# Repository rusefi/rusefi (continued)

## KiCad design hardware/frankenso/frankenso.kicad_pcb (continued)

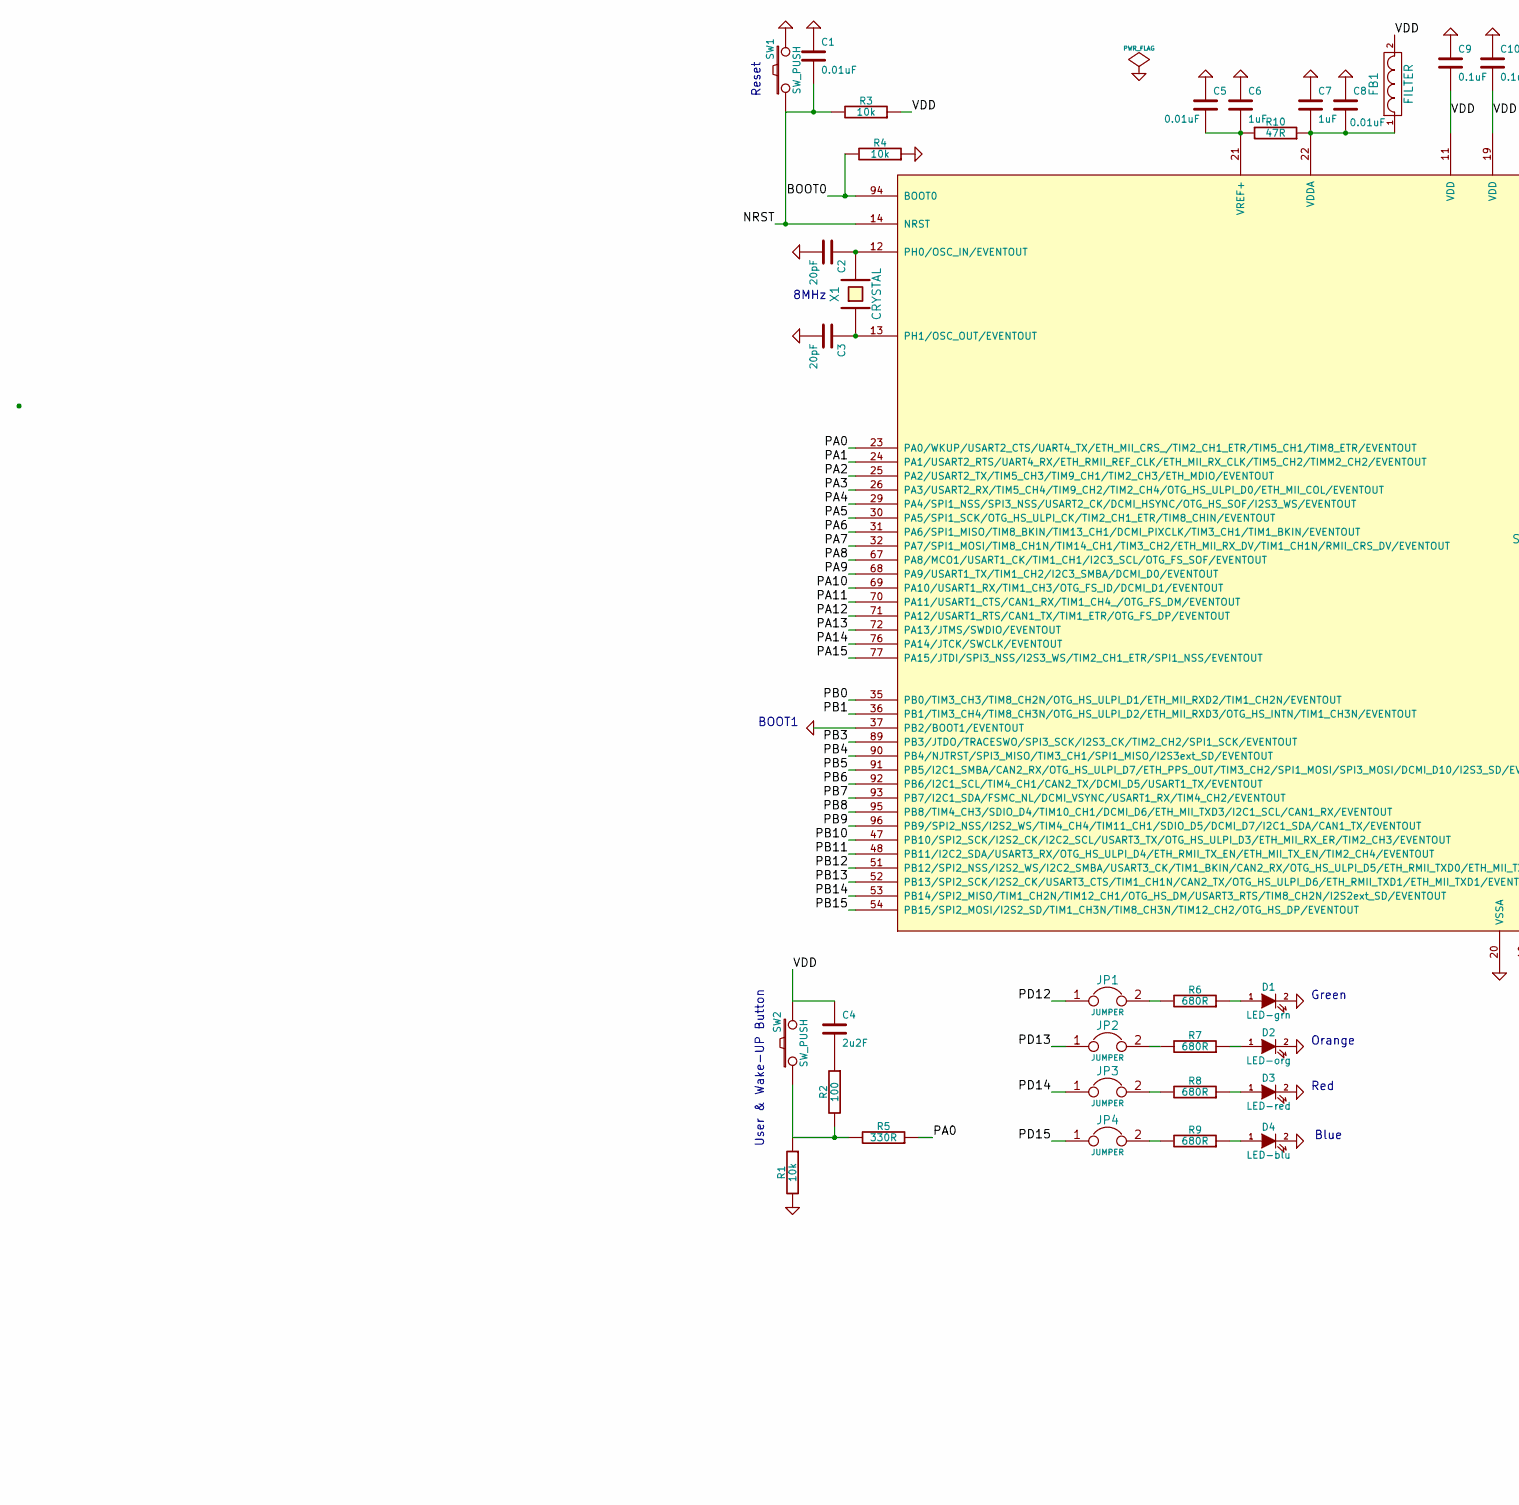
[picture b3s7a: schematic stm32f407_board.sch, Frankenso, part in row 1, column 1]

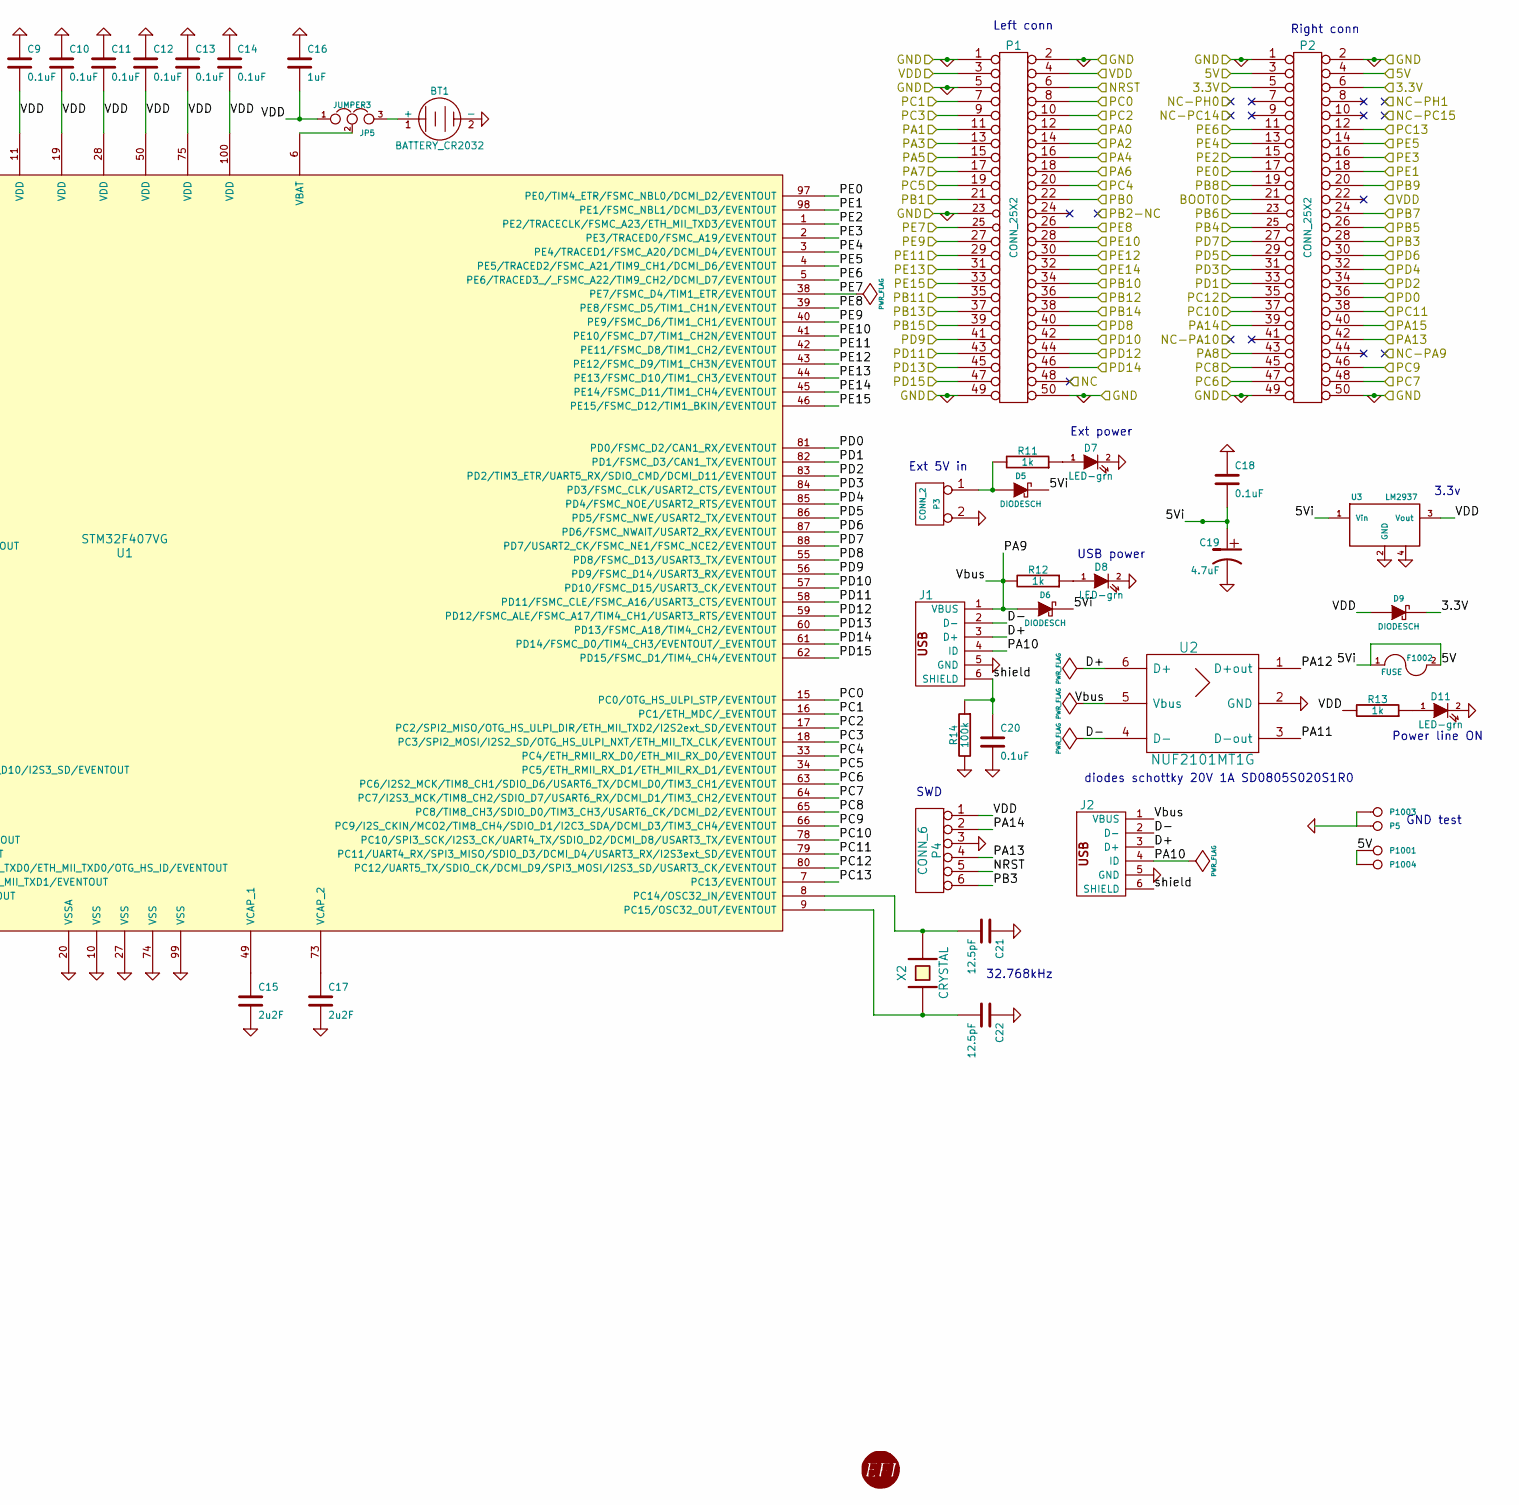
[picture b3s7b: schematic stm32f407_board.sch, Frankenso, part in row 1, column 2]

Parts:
BT1: BATTERY_CR2032; BATT_CR2032_MPD
C1, C5, C8: 0.01uF; SM0805
C2, C3: 20pF; SM0805
C4, C15, C17: 2u2F; SM0805
C6, C7, C16: 1uF; SM0805
C9, C10, C11, C12, C13, C14, C18, C20: 0.1uF; SM0805
C19: 4.7uF; SM0805
C21, C22: 12.5pF; SM0805
D1, D7, D8, D11: LED-grn; LED-0805_A
D2: LED-org; LED-0805_A
D3: LED-red; LED-0805_A
D4: LED-blu; LED-0805_A
D5, D6, D9: DIODESCH; SM0805-diode
F1002: FUSE; SM0805-diode
FB1: FILTER; SM0805
G1: LOGO; LOGO_F
J1: MINI-USB-5P-3400020P1
J2: MINI-USB-5P-3400020P1V; MINI-USB_RCTP_V-T_B
JP1, JP2, JP3, JP4: JUMPER; JUMPER-2
JP5: JUMPER3; SIL-3
P1, P2: CONN_25X2; PIN_ARRAY_25x2_A
P3: CONN_2; PIN_ARRAY_2_A
P4: CONN_6; PIN_ARRAY-6X1
P5, P1001, P1003, P1004: CONN_1; 1PIN_SMD
R1, R3, R4: 10k; SM0805
R2: 100; SM0805
R5: 330R; SM0805
R6, R7, R8, R9: 680R; SM0805
R10: 47R; SM0805
R11, R12, R13: 1k; SM0805
R14: 100k; SM0805
SW1, SW2: SW_PUSH; TL-1105
U1: STM32F407VG; TQFP_100
U2: NUF2101MT1G; SOT-457
U3: LM2937; SOT223
X1: CRYSTAL; HC-49V
X2: CRYSTAL; MC-306

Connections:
/DD_HIP9011/5V: C18.2, C19.1, D5.2 (K), D6.2 (K), F1002.1, F1002.2, P2.3, P2.4, P1001.1, P1004.1, U3.1 (Vin); also elsewhere on the board
/DD_HIP9011/CS: P1.22, U1.35 (PB0/TIM3_CH3/TIM8_CH2N/OTG_HS_ULPI_D1/E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); also elsewhere on the board
/DD_HIP9011/INT/HLD: P1.35, U1.48 (PB11/I2C2_SDA/USART3_RX/OTG_HS_ULPI_D4/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); also elsewhere on the board
/DD_HIP9011/OUT: P1.8, U1.15 (PC0/OTG_HS_ULPI_STP/EVENTOUT); also elsewhere on the board
/Misc_Vias/3.3V: D9.2 (K), P2.5, P2.6; also elsewhere on the board
/adc_amp_divider/OUT1: P1.10, U1.17 (PC2/SPI2_MISO/OTG_HS_ULPI_DIR/ETH_MII_T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); also elsewhere on the board
/adc_amp_divider/OUT2: P1.7, U1.16 (PC1/ETH_MDC/_EVENTOUT); also elsewhere on the board
/adc_amp_divider/OUT3: P1.12, R5.1, U1.23 (PA0/WKUP/USART2_CTS/UART4_TX/ETH_MII_CR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); also elsewhere on the board
/adc_amp_divider/OUT4: P1.9, U1.18 (PC3/SPI2_MOSI/I2S2_SD/OTG_HS_ULPI_NXT/E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); also elsewhere on the board
/adc_amp_divider/OUT5: P1.14, U1.25 (PA2/USART2_TX/TIM5_CH3/TIM9_CH1/TIM2_CH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); also elsewhere on the board
/adc_amp_divider/OUT6: P1.11, U1.24 (PA1/USART2_RTS/UART4_RX/ETH_RMII_REF_CL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); also elsewhere on the board
/adc_amp_divider/OUT7: P1.16, U1.29 (PA4/SPI1_NSS/SPI3_NSS/USART2_CK/DCMI_HS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); also elsewhere on the board
/adc_amp_divider/OUT8: P1.13, U1.26 (PA3/USART2_RX/TIM5_CH4/TIM9_CH2/TIM2_CH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); also elsewhere on the board
/adc_amp_divider/OUT9: P1.17, U1.32 (PA7/SPI1_MOSI/TIM8_CH1N/TIM14_CH1/TIM3_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); also elsewhere on the board
/adc_amp_divider/OUT10: P1.18, U1.31 (PA6/SPI1_MISO/TIM8_BKIN/TIM13_CH1/DCMI_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); also elsewhere on the board
/adc_amp_divider/OUT11: P1.19, U1.34 (PC5/ETH_RMII_RX_D1/ETH_MII_RX_D1/EVENTO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); also elsewhere on the board
/adc_amp_divider/OUT12: P1.20, U1.33 (PC4/ETH_RMII_RX_D0/ETH_MII_RX_D0/EVENTO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); also elsewhere on the board
/can_brd_1/CAN_RX: P1.36, U1.51 (PB12/SPI2_NSS/I2S2_WS/I2C2_SMBA/USART3_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); also elsewhere on the board
/can_brd_1/CAN_TX: P2.23, U1.92 (PB6/I2C1_SCL/TIM4_CH1/CAN2_TX/DCMI_D5/U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); also elsewhere on the board
/hi-lo/H_IN1: P2.48, U1.64 (PC7/I2S3_MCK/TIM8_CH2/SDIO_D7/USART6_RX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); also elsewhere on the board
/hi-lo/H_IN2: P1.32, U1.45 (PE14/FSMC_D11/TIM1_CH4/EVENTOUT); also elsewhere on the board
/hi-lo/H_IN3: P2.46, U1.66 (PC9/I2S_CKIN/MCO2/TIM8_CH4/SDIO_D1/I2C3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); also elsewhere on the board
/hi-lo/H_IN4: P1.30, U1.43 (PE12/FSMC_D9/TIM1_CH3N/EVENTOUT); also elsewhere on the board
/hi-lo/H_IN5: P1.26, U1.39 (PE8/FSMC_D5/TIM1_CH1N/EVENTOUT); also elsewhere on the board
/hi-lo/H_IN6: P1.28, U1.41 (PE10/FSMC_D7/TIM1_CH2N/EVENTOUT); also elsewhere on the board
/inj_12ch/INJ-01_5V: P2.11, U1.5 (PE6/TRACED3_/_FSMC_A22/TIM9_CH2/DCMI_D7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); also elsewhere on the board
/inj_12ch/INJ-02_5V: P2.14, U1.4 (PE5/TRACED2/FSMC_A21/TIM9_CH1/DCMI_D6/E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); also elsewhere on the board
/inj_12ch/INJ-03_5V: P2.27, U1.88 (PD7/USART2_CK/FSMC_NE1/FSMC_NCE2/EVENTO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); also elsewhere on the board
/inj_12ch/INJ-04_5V: P2.12, U1.7 (PC13/EVENTOUT); also elsewhere on the board
/inj_12ch/INJ-05_5V: P2.16, U1.2 (PE3/TRACED0/FSMC_A19/EVENTOUT); also elsewhere on the board
/inj_12ch/INJ-06_5V: P2.13, U1.3 (PE4/TRACED1/FSMC_A20/DCMI_D4/EVENTOUT); also elsewhere on the board
/inj_12ch/INJ-07_5V: P2.18, U1.98 (PE1/FSMC_NBL1/DCMI_D3/EVENTOUT); also elsewhere on the board
/inj_12ch/INJ-08_5V: P2.15, U1.1 (PE2/TRACECLK/FSMC_A23/ETH_MII_TXD3/EVEN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); also elsewhere on the board
/inj_12ch/INJ-09_5V: P2.20, U1.96 (PB9/SPI2_NSS/I2S2_WS/TIM4_CH4/TIM11_CH1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); also elsewhere on the board
/inj_12ch/INJ-10_5V: P2.17, U1.97 (PE0/TIM4_ETR/FSMC_NBL0/DCMI_D2/EVENTOUT); also elsewhere on the board
/inj_12ch/INJ-11_5V: P2.19, U1.95 (PB8/TIM4_CH3/SDIO_D4/TIM10_CH1/DCMI_D6/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); also elsewhere on the board
/inj_12ch/INJ-12_5V: P2.24, U1.93 (PB7/I2C1_SDA/FSMC_NL/DCMI_VSYNC/USART1_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); also elsewhere on the board
/mmc_usb_1/CS_SD_MODULE: P2.32, U1.85 (PD4/FSMC_NOE/USART2_RTS/EVENTOUT); also elsewhere on the board
/stm32f407_board/BOOT0: P2.21, R4.2, U1.94 (BOOT0); also elsewhere on the board
/stm32f407_board/D+: J1.3 (D+), J2.3 (D+), U2.6 (D+)
/stm32f407_board/D-: J1.2 (D-), J2.2 (D-), U2.4 (D-)
/stm32f407_board/NRST: C1.2, P1.6, P4.5, R3.2, SW1.1, U1.14 (NRST)
/stm32f407_board/PA5: P1.15, U1.30 (PA5/SPI1_SCK/OTG_HS_ULPI_CK/TIM2_CH1_ET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); also elsewhere on the board
/stm32f407_board/PA9: D6.1 (A), J1.1 (VBUS), J2.1 (VBUS), R12.2, U1.68 (PA9/USART1_TX/TIM1_CH2/I2C3_SMBA/DCMI_D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), U2.5 (Vbus)
/stm32f407_board/PA10: J1.4 (ID), J2.4 (ID), U1.69 (PA10/USART1_RX/TIM1_CH3/OTG_FS_ID/DCMI_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)
/stm32f407_board/PA11: U1.70 (PA11/USART1_CTS/CAN1_RX/TIM1_CH4_/OTG_F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), U2.3 (D-out)
/stm32f407_board/PA12: U1.71 (PA12/USART1_RTS/CAN1_TX/TIM1_ETR/OTG_FS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), U2.1 (D+out)
/stm32f407_board/PA15: P2.40, U1.77 (PA15/JTDI/SPI3_NSS/I2S3_WS/TIM2_CH1_ETR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); also elsewhere on the board
/stm32f407_board/PB1: P1.21, U1.36 (PB1/TIM3_CH4/TIM8_CH3N/OTG_HS_ULPI_D2/E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); also elsewhere on the board
/stm32f407_board/PB3: P2.28, P4.6, U1.89 (PB3/JTDO/TRACESWO/SPI3_SCK/I2S3_CK/TIM2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); also elsewhere on the board
/stm32f407_board/PB5: P2.26, U1.91 (PB5/I2C1_SMBA/CAN2_RX/OTG_HS_ULPI_D7/ET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); also elsewhere on the board
/stm32f407_board/PB10: P1.34, U1.47 (PB10/SPI2_SCK/I2S2_CK/I2C2_SCL/USART3_T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); also elsewhere on the board
/stm32f407_board/PB13: P1.37, U1.52 (PB13/SPI2_SCK/I2S2_CK/USART3_CTS/TIM1_C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); also elsewhere on the board
/stm32f407_board/PB14: P1.38, U1.53 (PB14/SPI2_MISO/TIM1_CH2N/TIM12_CH1/OTG_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); also elsewhere on the board
/stm32f407_board/PB15: P1.39, U1.54 (PB15/SPI2_MOSI/I2S2_SD/TIM1_CH3N/TIM8_C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); also elsewhere on the board
/stm32f407_board/PC6: P2.47, U1.63 (PC6/I2S2_MCK/TIM8_CH1/SDIO_D6/USART6_TX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); also elsewhere on the board
/stm32f407_board/PC8: P2.45, U1.65 (PC8/TIM8_CH3/SDIO_D0/TIM3_CH3/USART6_CK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); also elsewhere on the board
/stm32f407_board/PC10: P2.37, U1.78 (PC10/SPI3_SCK/I2S3_CK/UART4_TX/SDIO_D2/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); also elsewhere on the board
/stm32f407_board/PC11: P2.38, U1.79 (PC11/UART4_RX/SPI3_MISO/SDIO_D3/DCMI_D4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); also elsewhere on the board
/stm32f407_board/PC12: P2.35, U1.80 (PC12/UART5_TX/SDIO_CK/DCMI_D9/SPI3_MOSI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); also elsewhere on the board
/stm32f407_board/PD0: P2.36, U1.81 (PD0/FSMC_D2/CAN1_RX/EVENTOUT); also elsewhere on the board
/stm32f407_board/PD1: P2.33, U1.82 (PD1/FSMC_D3/CAN1_TX/EVENTOUT); also elsewhere on the board
/stm32f407_board/PD2: P2.34, U1.83 (PD2/TIM3_ETR/UART5_RX/SDIO_CMD/DCMI_D11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); also elsewhere on the board
/stm32f407_board/PD3: P2.31, U1.84 (PD3/FSMC_CLK/USART2_CTS/EVENTOUT); also elsewhere on the board
/stm32f407_board/PD5: P2.29, U1.86 (PD5/FSMC_NWE/USART2_TX/EVENTOUT); also elsewhere on the board
/stm32f407_board/PD6: P2.30, U1.87 (PD6/FSMC_NWAIT/USART2_RX/EVENTOUT); also elsewhere on the board
/stm32f407_board/PD8: P1.40, U1.55 (PD8/FSMC_D13/USART3_TX/EVENTOUT); also elsewhere on the board
/stm32f407_board/PD9: P1.41, U1.56 (PD9/FSMC_D14/USART3_RX/EVENTOUT); also elsewhere on the board
/stm32f407_board/PD10: P1.42, U1.57 (PD10/FSMC_D15/USART3_CK/EVENTOUT); also elsewhere on the board
/stm32f407_board/PD11: P1.43, U1.58 (PD11/FSMC_CLE/FSMC_A16/USART3_CTS/EVENT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); also elsewhere on the board
/stm32f407_board/PD13: JP2.1, P1.45, U1.60 (PD13/FSMC_A18/TIM4_CH2/EVENTOUT)
/stm32f407_board/PD14: JP3.1, P1.46, U1.61 (PD14/FSMC_D0/TIM4_CH3/EVENTOUT/_EVENTOUT)
/stm32f407_board/PD15: JP4.1, P1.47, U1.62 (PD15/FSMC_D1/TIM4_CH4/EVENTOUT)
/stm32f407_board/PE7: P1.25, U1.38 (PE7/FSMC_D4/TIM1_ETR/EVENTOUT); also elsewhere on the board
/stm32f407_board/PE9: P1.27, U1.40 (PE9/FSMC_D6/TIM1_CH1/EVENTOUT); also elsewhere on the board
/stm32f407_board/PE11: P1.29, U1.42 (PE11/FSMC_D8/TIM1_CH2/EVENTOUT); also elsewhere on the board
/stm32f407_board/PE13: P1.31, U1.44 (PE13/FSMC_D10/TIM1_CH3/EVENTOUT); also elsewhere on the board
/stm32f407_board/PE15: P1.33, U1.46 (PE15/FSMC_D12/TIM1_BKIN/EVENTOUT); also elsewhere on the board
/stm32f407_board/VDD: C4.1, C9.2, C10.2, C11.2, C12.2, C13.2, C14.2, C16.2, D9.1 (A), FB1.2, JP5.1, P1.3, P1.4, P4.1, R3.1, R13.2, SW2.2, U1.11 (VDD), U1.19 (VDD), U1.28 (VDD), U1.50 (VDD), U1.75 (VDD), U1.100 (VDD), U3.3 (Vout)
/stm32f407_board/shield: C20.1, J1.6 (SHIELD), J2.6 (SHIELD), R14.1
/thermocouple1//CS: JP1.1, P1.44, U1.59 (PD12/FSMC_ALE/FSMC_A17/TIM4_CH1/USART3_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); also elsewhere on the board
/thermocouple1/MISO: P2.25, U1.90 (PB4/NJTRST/SPI3_MISO/TIM3_CH1/SPI1_MISO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); also elsewhere on the board
/thermocouple2//CS: P2.39, P4.2, U1.76 (PA14/JTCK/SWCLK/EVENTOUT); also elsewhere on the board
/thermocouple3//CS: P2.43, U1.67 (PA8/MCO1/USART1_CK/TIM1_CH1/I2C3_SCL/OT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); also elsewhere on the board
/thermocouple4//CS: P2.42, P4.4, U1.72 (PA13/JTMS/SWDIO/EVENTOUT); also elsewhere on the board
GND: BT1.2 (-), C1.1, C2.2, C3.2, C5.1, C6.1, C7.1, C8.1, C9.1, C10.1, C11.1, C12.1, C13.1, C14.1, C15.2, C16.1, C17.2, C18.1, C19.2, C20.2, C21.1, C22.1, D1.2 (K), D2.2 (K), D3.2 (K), D4.2 (K), D7.2 (K), D8.2 (K), D11.2 (K), J1.5 (GND), J2.5 (GND), P1.1, P1.2, P1.5, P1.23, P1.49, P1.50, P2.1, P2.2, P2.49, P2.50, P3.2 (PM), P4.3, P5.1, P1003.1, R1.2, R4.1, R14.2, SW1.2, U1.10 (VSS), U1.20 (VSSA), U1.27 (VSS), U1.37 (PB2/BOOT1/EVENTOUT), U1.74 (VSS), U1.99 (VSS), U2.2 (GND), U3.2 (GND), U3.4; also elsewhere on the board
unnamed: C5.2, C6.2, R10.2, U1.21 (VREF+)
unnamed: C22.2, U1.9 (PC15/OSC32_OUT/EVENTOUT), X2.1
unnamed: C21.2, U1.8 (PC14/OSC32_IN/EVENTOUT), X2.2
unnamed: C2.1, U1.12 (PH0/OSC_IN/EVENTOUT), X1.2
unnamed: D4.1 (A), R9.1
unnamed: D7.1 (A), R11.1
unnamed: D8.1 (A), R12.1
unnamed: D11.1 (A), R13.1
unnamed: D1.1 (A), R6.1
unnamed: D2.1 (A), R7.1
unnamed: D3.1 (A), R8.1
unnamed: BT1.1 (+), JP5.3
unnamed: JP4.2, R9.2
unnamed: JP3.2, R8.2
unnamed: JP2.2, R7.2
unnamed: JP1.2, R6.2
unnamed: R1.1, R2.2, R5.2, SW2.1
unnamed: D5.1 (A), P3.1, R11.2
unnamed: JP5.2, U1.6 (VBAT)
unnamed: C3.1, U1.13 (PH1/OSC_OUT/EVENTOUT), X1.1
unnamed: C17.1, U1.73 (VCAP_2)
unnamed: C15.1, U1.49 (VCAP_1)
unnamed: C4.2, R2.1
unnamed: C7.2, C8.2, FB1.1, R10.1, U1.22 (VDDA)

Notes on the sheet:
Left conn
Right conn
Reset
User & Wake-UP Button
Green
Orange
Red
Blue
Ext 5V in
SWD
USB power
Ext power
Power line ON
3.3v
8MHz
32.768kHz
diodes schottky 20V 1A SD0805S020S1R0
BOOT1
GND test

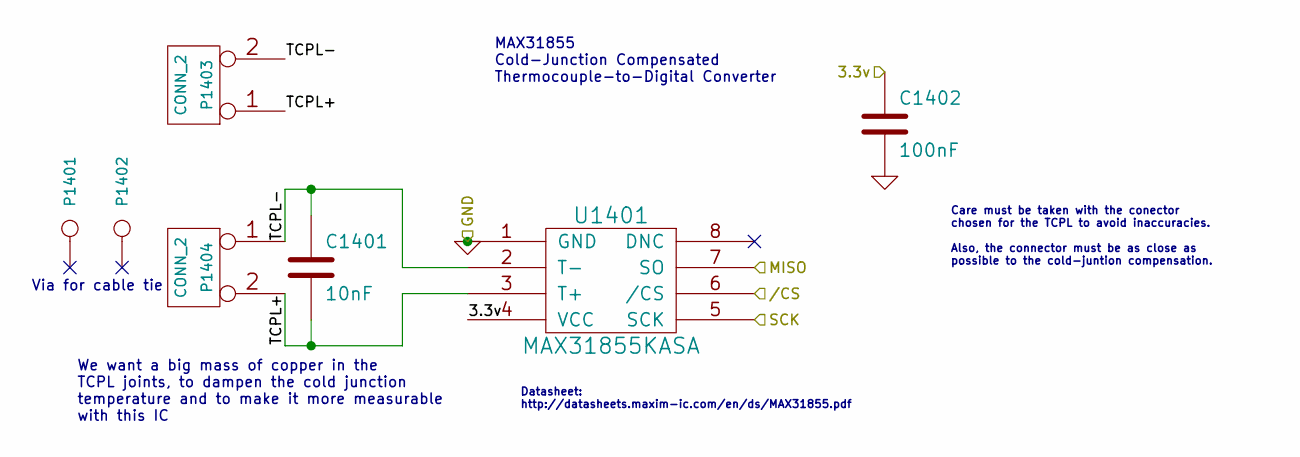
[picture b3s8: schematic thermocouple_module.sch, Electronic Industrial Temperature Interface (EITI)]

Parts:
C1101: 10nF; SM0805-SM0603
C1102: 100nF; SM0805-SM0603
P1101, P1102: CONN_1; 1pin
P1103: CONN_2; SIL-2
P1104: CONN_2; tcpl_PCC-SMP
U1101: MAX31855KASA; SO8E

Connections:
/Misc_Vias/3.3V: C1102.1, U1101.4 (VCC); also elsewhere on the board
/stm32f407_board/PB3: U1101.5 (SCK); also elsewhere on the board
/thermocouple1//CS: U1101.6 (/CS); also elsewhere on the board
/thermocouple1/MISO: U1101.7 (SO); also elsewhere on the board
/thermocouple1/TCPL+: C1101.2, P1103.1, P1104.2 (PM), U1101.3 (T+)
/thermocouple1/TCPL-: C1101.1, P1103.2 (PM), P1104.1, U1101.2 (T-)
GND: C1102.2, U1101.1 (GND); also elsewhere on the board

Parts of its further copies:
C1201, C1301, C1401: 10nF; SM0805-SM0603
C1202, C1302, C1402: 100nF; SM0805-SM0603
P1201, P1202, P1301, P1302, P1401, P1402: CONN_1; 1pin
P1203, P1303, P1403: CONN_2; SIL-2
P1204, P1304, P1404: CONN_2; tcpl_PCC-SMP
U1201, U1301, U1401: MAX31855KASA; SO8E

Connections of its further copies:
/Misc_Vias/3.3V: C1202.1, C1302.1, C1402.1, U1201.4 (VCC), U1301.4 (VCC), U1401.4 (VCC); also elsewhere on the board
/stm32f407_board/PB3: U1201.5 (SCK), U1301.5 (SCK), U1401.5 (SCK); also elsewhere on the board
/thermocouple1/MISO: U1201.7 (SO), U1301.7 (SO), U1401.7 (SO); also elsewhere on the board
/thermocouple2//CS: U1201.6 (/CS); also elsewhere on the board
/thermocouple2/TCPL+: C1201.2, P1203.1, P1204.2 (PM), U1201.3 (T+)
/thermocouple2/TCPL-: C1201.1, P1203.2 (PM), P1204.1, U1201.2 (T-)
/thermocouple3//CS: U1301.6 (/CS); also elsewhere on the board
/thermocouple3/TCPL+: C1301.2, P1303.1, P1304.2 (PM), U1301.3 (T+)
/thermocouple3/TCPL-: C1301.1, P1303.2 (PM), P1304.1, U1301.2 (T-)
/thermocouple4//CS: U1401.6 (/CS); also elsewhere on the board
/thermocouple4/TCPL+: C1401.2, P1403.1, P1404.2 (PM), U1401.3 (T+)
/thermocouple4/TCPL-: C1401.1, P1403.2 (PM), P1404.1, U1401.2 (T-)
GND: C1202.2, C1302.2, C1402.2, U1201.1 (GND), U1301.1 (GND), U1401.1 (GND); also elsewhere on the board

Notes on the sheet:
We want a big mass of copper in the TCPL joints, to dampen the cold junction temperature and to make it more measurable with this IC
Via for cable tie
Care must be taken with the conector chosen for the TCPL to avoid inaccuracies. Also, the connector must be as close as possible to the cold-juntion compensation.
MAX31855 Cold-Junction Compensated Thermocouple-to-Digital Converter
Datasheet: http://datasheets.maxim-ic.com/en/ds/MAX31855.pdf

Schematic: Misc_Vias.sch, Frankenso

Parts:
JPO2, JPO3, JPO6, JPO7, JPO8, JPO9: TEST-gnd; SIL-2
P7, P8, P14: pin_array_12x2
P24, P25, P26: pin_array_8x2
P27: CONN_6X2; pin_array_6x2
P28, P35, P36, P42, P43: CONN_12X2; pin_array_12x2
P29, P34, P37, P38, P41, P45, P47: CONN_5X2; PIN_ARRAY_5x2
P31, P32, P48: CONN_4X2; pin_array_4x2
P33, P39, P40, P44, P46: CONN_8X2; pin_array_8x2
P49: CONN_2X2; PIN_ARRAY_2X2
P50: CONN_13X2; pin_array_13x2
TEST2: TEST-C-C; SIL-2

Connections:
/DD_HIP9011/5V: JPO8.1, JPO8.2, P14.1, P26.1, P47.10, P50.5, P50.21; also elsewhere on the board
/Misc_Vias/3.3V: JPO9.1, JPO9.2, P14.3, P26.3, P50.3, P50.23; also elsewhere on the board
/Misc_Vias/CAM: TEST2.1; also elsewhere on the board
/Misc_Vias/CRANK: TEST2.2; also elsewhere on the board
/hi-lo/12V: JPO6.1, JPO6.2; also elsewhere on the board
GND: JPO2.1, JPO2.2, JPO3.1, JPO3.2, JPO7.1, JPO7.2, P14.7, P26.7, P47.9, P50.1, P50.25 (P24); also elsewhere on the board

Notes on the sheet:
These two jumpers are here to accomodate stm32f4discovery
That's alternative signal OUTPUT - these traces should be routable to PC6 and PA5 via jumpers. Aleternative to W212 and W212 routung of op-amps ch 11 and ch 12
PROTO AREA
These four jumpers are test points

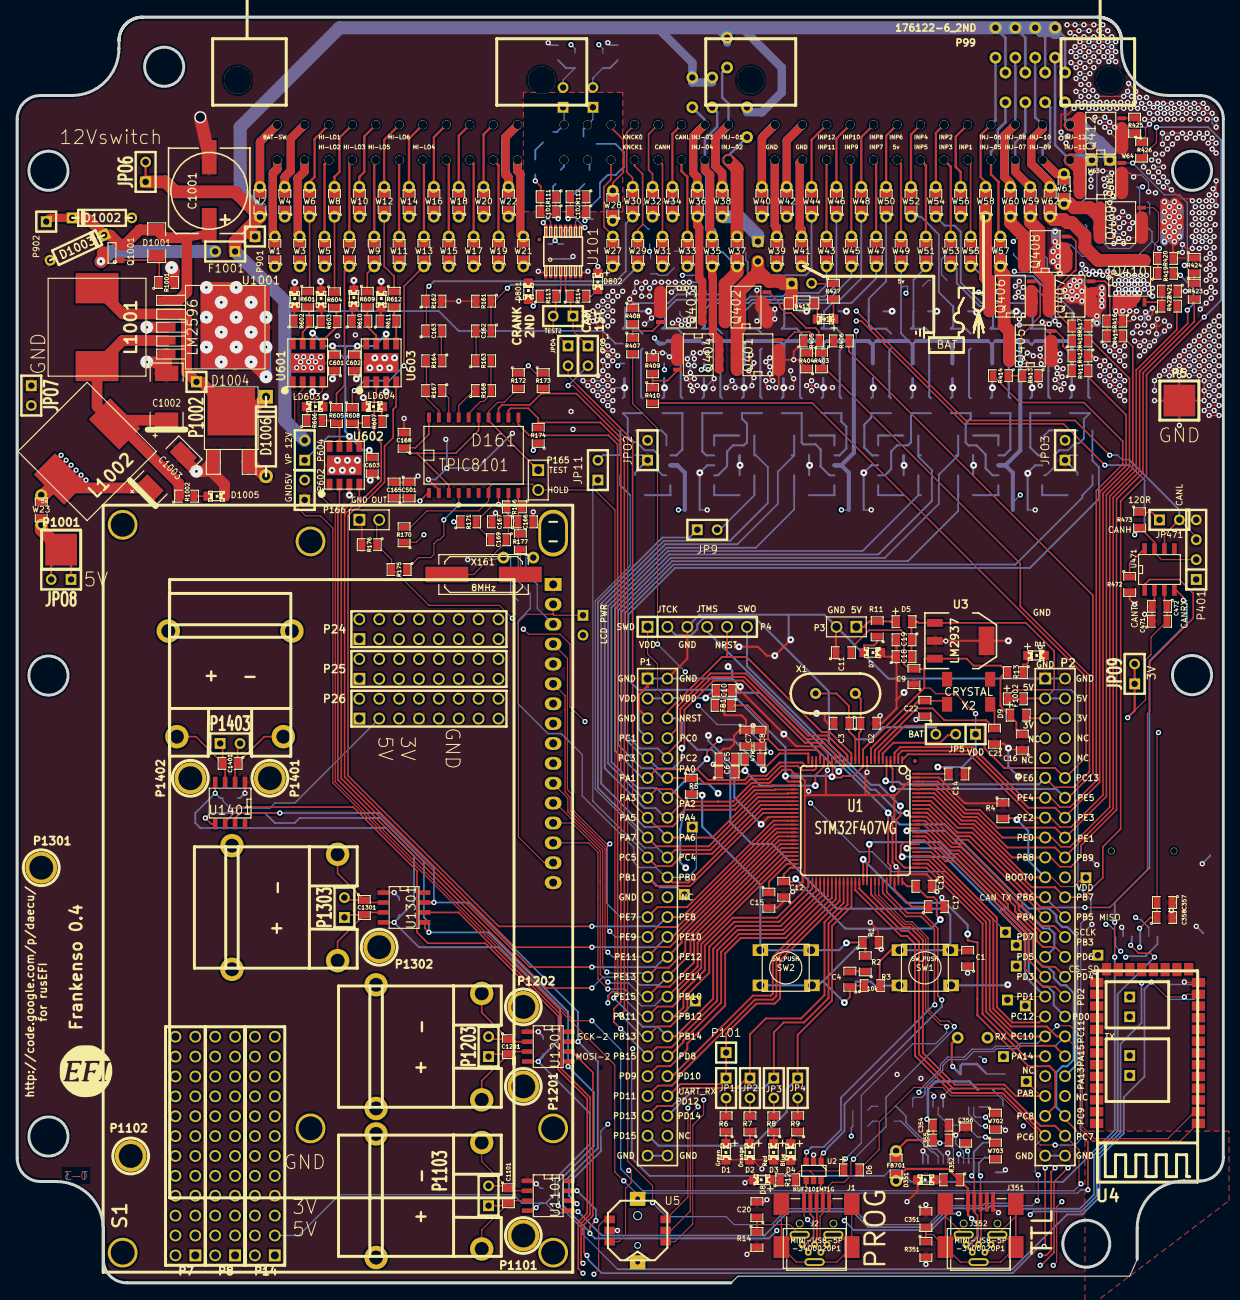
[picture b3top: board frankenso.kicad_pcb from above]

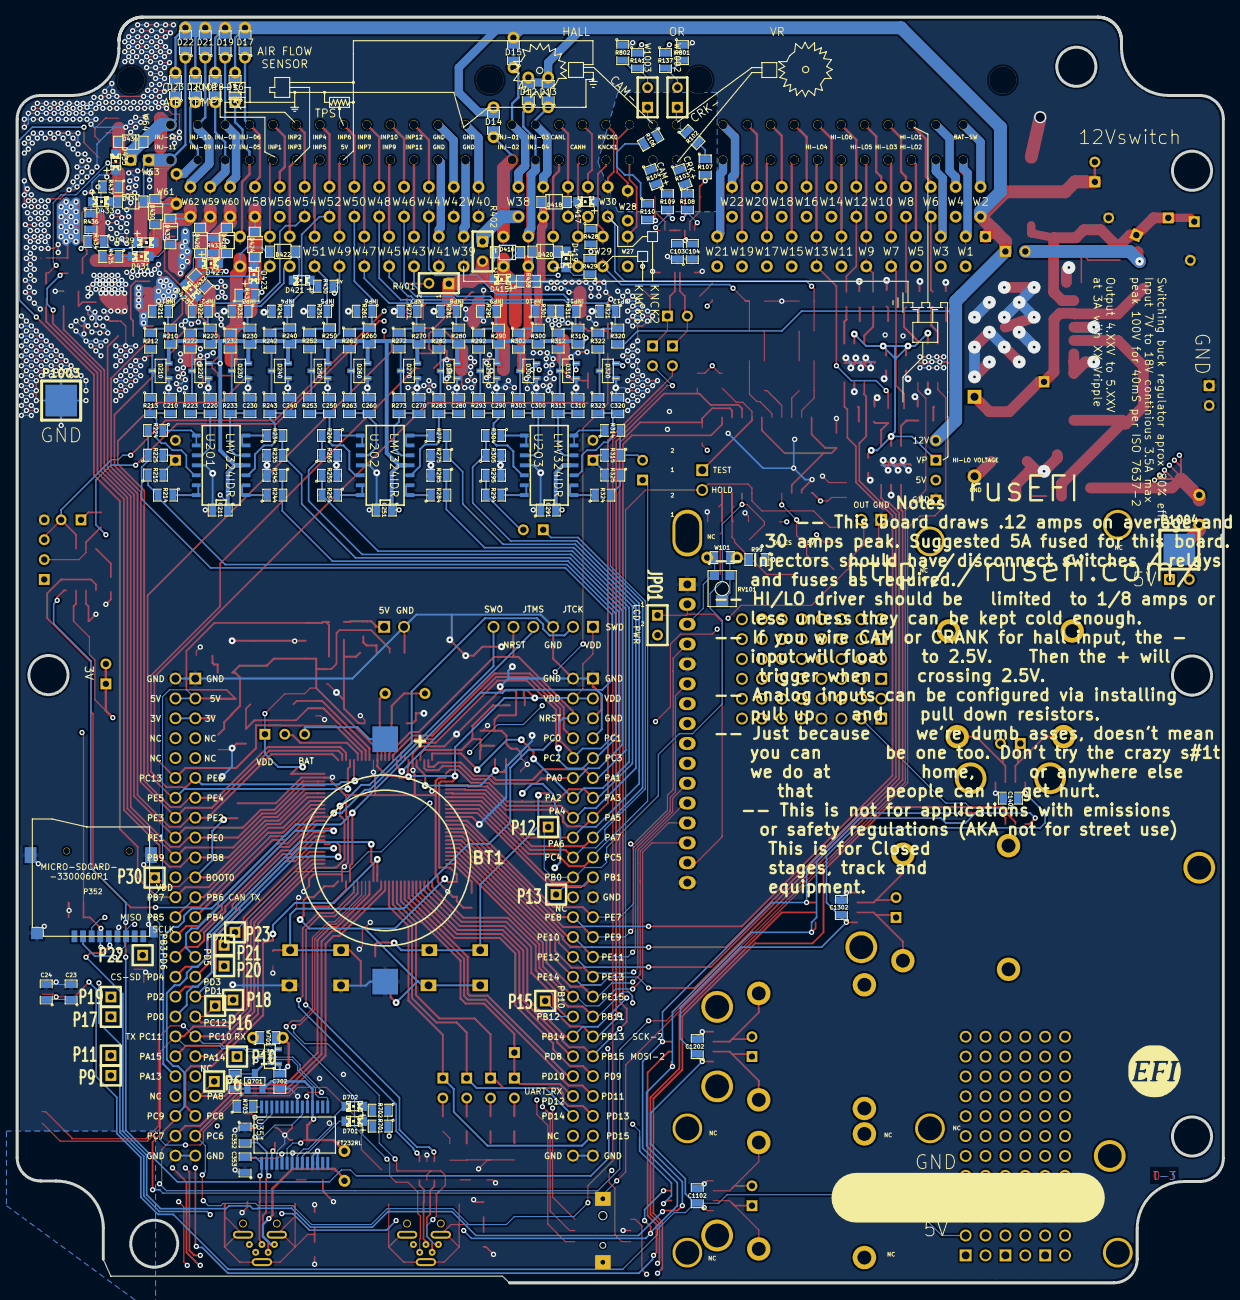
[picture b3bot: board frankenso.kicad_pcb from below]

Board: 4 copper layers, 154.1 x 161.7 mm, 526 parts (209 on the bottom side), 359 nets.

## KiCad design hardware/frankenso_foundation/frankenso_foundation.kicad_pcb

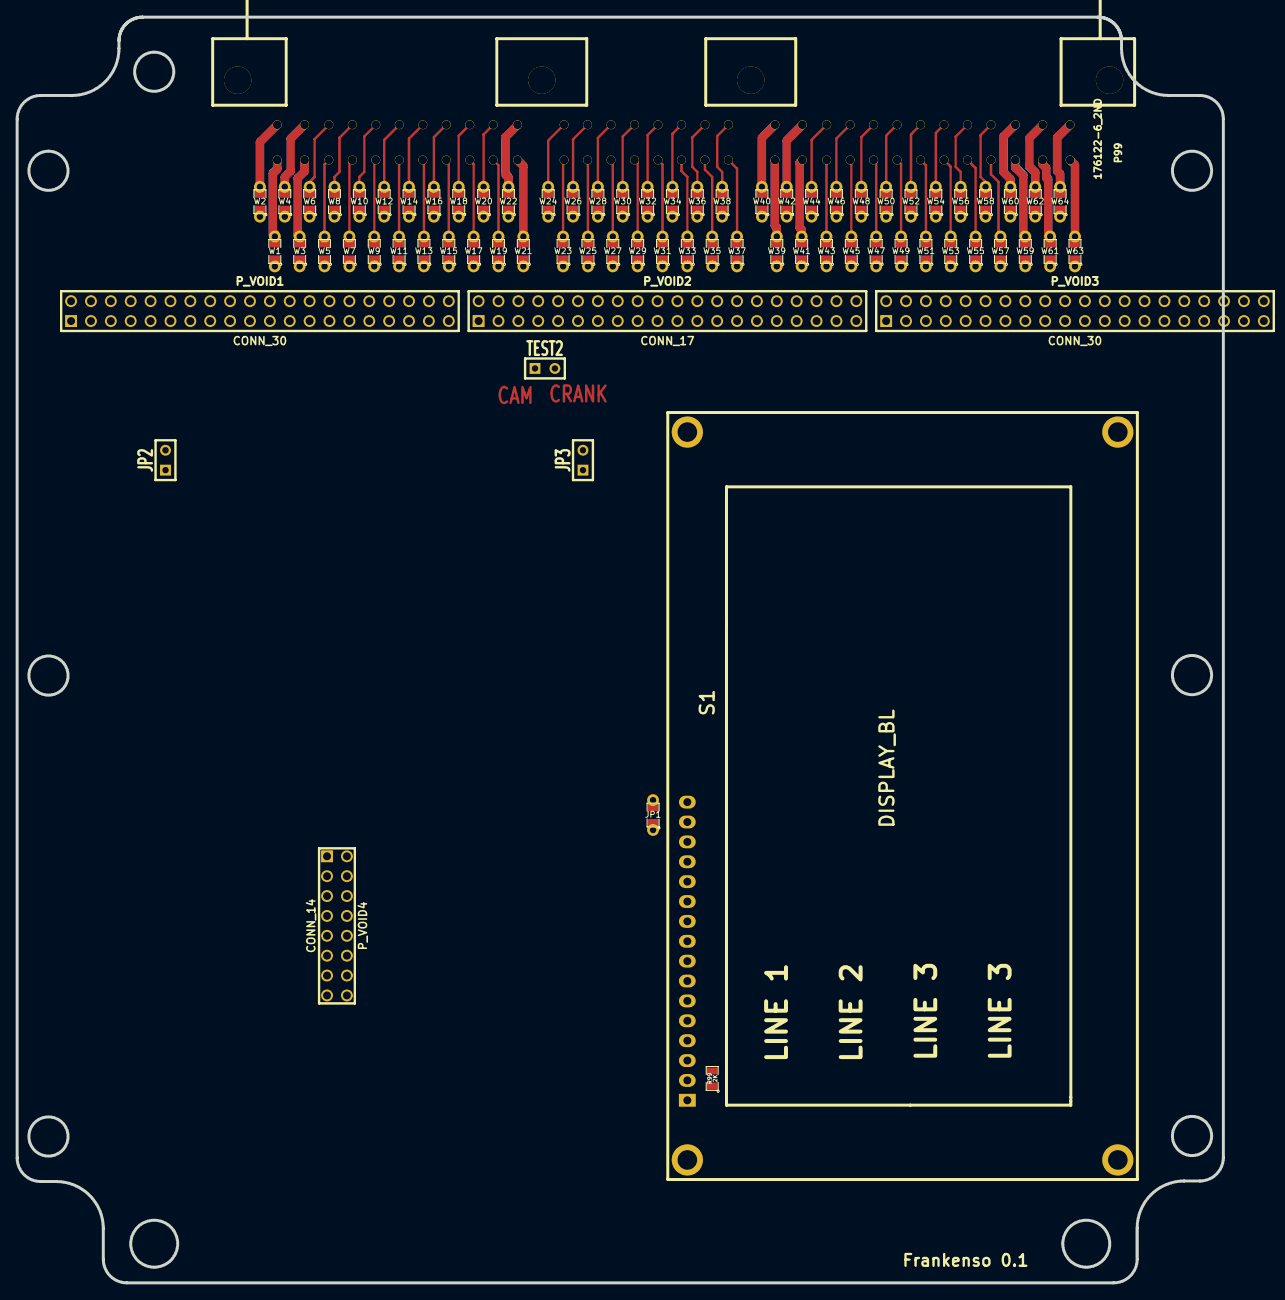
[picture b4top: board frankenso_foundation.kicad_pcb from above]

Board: 2 copper layers, 154.1 x 161.7 mm, 75 parts (0 on the bottom side), 120 nets.

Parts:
JP1: TEST; SM0805_jumper
JP2, JP3: TEST; SIL-2
P99: 176122-6_2ND; 176122-6_2nd
P_VOID1, P_VOID3: CONN_30; PIN_ARRAY_20X2
P_VOID2: CONN_17; PIN_ARRAY_20X2
P_VOID4: CONN_14; pin_array_8x2
R99: 2K; SM0805
S1: DISPLAY_BL; DISPLAY_4x20_BL
TEST2: TEST; SIL-2
W1, W2, W3, W4, W5, W6, W7, W8, W9, W10, W11, W12, W13, W14, W15, W16, W17, W18, W19, W20, W21, W22, W23, W24, W25, W26, W27, W28, W29, W30, W31, W32, W33, W34, W35, W36, W37, W38, W39, W40, W41, W42, W43, W44, W45, W46, W47, W48, W49, W50, W51, W52, W53, W54, W55, W56, W57, W58, W59, W60, W61, W62, W63, W64: TEST; SM0805_jumper

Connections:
/2C: P_VOID2.3, W25.1
/2D: P_VOID2.4, W26.1
/2K: P_VOID2.11, W33.1
/2M: P_VOID2.13, W35.1
/2O: P_VOID2.15, W37.1
/3F: P_VOID3.6, W44.1
/3H: P_VOID3.8, W46.1
/5V: JP1.2, P_VOID3.11
/12V: P_VOID1.2, W2.1
/12V-CONST: P_VOID1.1, W1.1
/AC-RELAY: P_VOID1.10, W10.1
/AC-SW: P_VOID1.17, W17.1
/BLOWER-SW: P_VOID1.19, W19.1
/CAM: P_VOID1.24, TEST2.1
/CAM+: P_VOID2.7, W29.1
/CAM-: P_VOID2.8, W30.1
/CANH: P_VOID2.1, W23.1
/CANL: P_VOID2.2, W24.1
/COOL-FAN: P_VOID1.18, W18.1
/CPU-GND: P_VOID3.3, W41.1
/CRANK: P_VOID1.23, TEST2.2
/CRK2+: P_VOID2.9, W31.1
/CRK2-: P_VOID2.10, W32.1
/DIAG: P_VOID1.4, W4.1
/DIAG-1K: P_VOID1.11, W11.1
/HD44780_CS: P_VOID4.9, S1.6
/HD44780_D4: P_VOID4.4, S1.11
/HD44780_D5: P_VOID4.3, S1.12
/HD44780_D6: P_VOID4.2, S1.13
/HD44780_D7: P_VOID4.1, S1.14
/HD44780_RS: P_VOID4.11, S1.4
/HD44780_VCC: JP1.1, P_VOID4.13, S1.2, S1.A
/HEADLIGHT-SW: P_VOID1.21, W21.1
/HL1: P_VOID1.6, W6.1
/HL2: P_VOID1.7, W7.1
/HL3: P_VOID1.8, W8.1
/HL4: P_VOID1.9, W9.1
/HL5: P_VOID1.12, W12.1
/HL6: P_VOID1.13, W13.1
/INJ-07: P_VOID3.24, W62.1
/INJ-10: P_VOID2.16, W38.1
/INJ-11: P_VOID2.14, W36.1
/INJ-12: P_VOID2.12, W34.1
/INPUT-GND: P_VOID3.4, W42.1
/KNOCK1: P_VOID2.5, W27.1
/KNOCK2: P_VOID2.6, W28.1
/MUL: P_VOID1.5, W5.1
/NEUTRAL-CLUTCH-SW: P_VOID1.22, W22.1
/OUTPUT-GND: P_VOID3.2, W40.1
/REAR-DEFROSTER-SW: P_VOID1.20, W20.1
/START-SIG: P_VOID1.3, W3.1
/STEERING-SW: P_VOID1.16, W16.1
/STOP-LIGHT: P_VOID1.15, W15.1
/TPS-IDL-SW: P_VOID1.14, W14.1
GND: JP2.1, JP2.2, JP3.1, JP3.2, P_VOID3.1, P_VOID4.10, P_VOID4.12, P_VOID4.14, R99.1, S1.1, S1.5, S1.K
unnamed: P99.22, W22.2
unnamed: P99.7, W13.2
unnamed: P99.18, W14.2
unnamed: P99.8, W15.2
unnamed: P99.19, W16.2
unnamed: P99.9, W17.2
unnamed: P99.20, W18.2
unnamed: P99.10, W19.2
unnamed: P99.21, W20.2
unnamed: P99.11, W21.2
unnamed: P99.17, W12.2
unnamed: P99.23, W23.2
unnamed: P99.31, W24.2
unnamed: P99.24, W25.2
unnamed: P99.32, W26.2
unnamed: P99.25, W27.2
unnamed: P99.33, W28.2
unnamed: P99.26, W29.2
unnamed: P99.34, W30.2
unnamed: P99.2, W3.2
unnamed: P99.1, W1.2
unnamed: P99.12, W2.2
unnamed: P99.27, W31.2
unnamed: P99.13, W4.2
unnamed: P99.3, W5.2
unnamed: P99.14, W6.2
unnamed: P99.4, W7.2
unnamed: P99.15, W8.2
unnamed: P99.5, W9.2
unnamed: P99.16, W10.2
unnamed: P99.6, W11.2
unnamed: P99.61, W58.2
unnamed: P99.57, W50.2
unnamed: P99.45, W51.2
unnamed: P99.58, W52.2
unnamed: P99.46, W53.2
unnamed: P99.59, W54.2
unnamed: P99.47, W55.2
unnamed: P99.60, W56.2
unnamed: P99.48, W57.2
unnamed: P99.44, W49.2
unnamed: P99.49, W59.2
unnamed: P99.62, W60.2
unnamed: P99.50, W61.2
unnamed: P99.63, W62.2
unnamed: P99.51, W63.2
unnamed: P99.64, W64.2
unnamed: P99.52, W40.2
unnamed: P99.35, W32.2
unnamed: P99.28, W33.2
unnamed: P99.36, W34.2
unnamed: P99.29, W35.2
unnamed: P99.37, W36.2
unnamed: P99.30, W37.2
unnamed: P99.38, W38.2
unnamed: P99.39, W39.2
unnamed: P99.40, W41.2
unnamed: P99.53, W42.2
unnamed: P99.41, W43.2
unnamed: P99.54, W44.2
unnamed: P99.42, W45.2
unnamed: P99.55, W46.2
unnamed: P99.43, W47.2
unnamed: P99.56, W48.2
unnamed: R99.2, S1.3
